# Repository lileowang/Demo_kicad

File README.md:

# Demo_kicad
Demo how to use Kicad for capturing circuit schematics and PCB layout

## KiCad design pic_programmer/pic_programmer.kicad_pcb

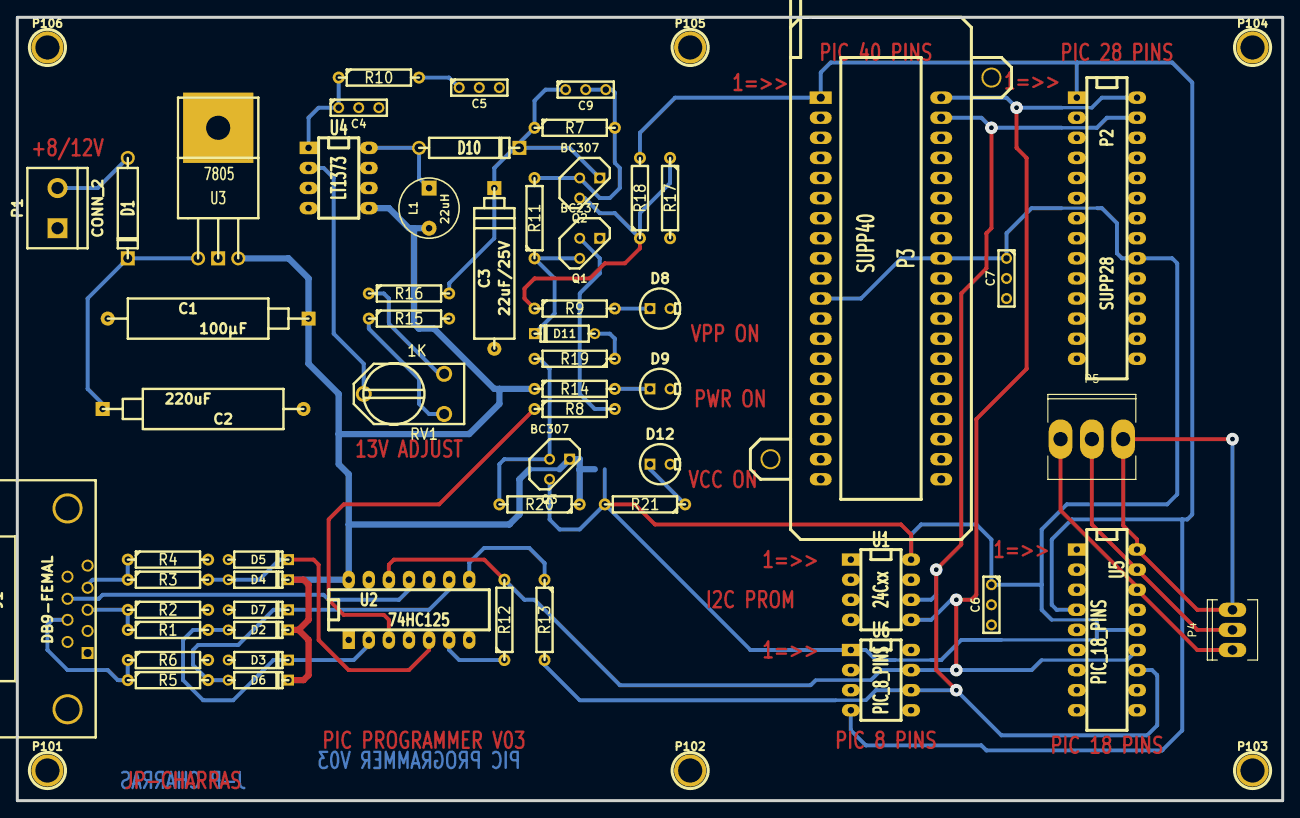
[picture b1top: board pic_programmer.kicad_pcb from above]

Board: 2 copper layers, 160.0 x 99.1 mm, 65 parts (1 on the bottom side), 37 nets.

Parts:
C1: 100µF; CP10
C2: 220uF; CP10
C3: 22uF/25V; CP8
C4: 0; C1-1
C5: 10nF; C1-1
C6, C7: 100nF; C1-1
C9: 220nF; C1-1
D1: 1N4004; D5
D2, D3, D4, D5, D6, D7, D11: BAT43; D3
D8: RED-LED; LEDV
D9: GREEN-LED; LEDV
D10: SCHOTTKY; D5
D12: YELLOW-LED; LEDV
J1: DB9-FEMAL; DB9FC
JP1: JUMPER; GS2
L1: 22uH; INDUCTOR_V
P1: CONN_2; bornier2
P2: SUPP28; DIP-28__300_ELL
P3: SUPP40; 40tex-Ell600
P4: CONN_01X03; Socket_MOLEX-KK-RM2-54mm_Lock_3pin_straight
P5: CONN_01X03; Socket_MOLEX-KK-RM3-96mm_Lock_3pin_straight
P101, P102, P103, P104, P105, P106: CONN_1; 1pin-4
Q1: BC237; TO92
Q2, Q3: BC307; TO92
R1, R2, R3, R4, R5, R6, R7: 10K; R4
R8: 1K; R4
R9, R19, R20: 2.2K; R4
R10: 5,1K; R4
R11, R17: 22K; R4
R12, R13, R14, R21: 470; R4
R15: 6.2K; R4
R16: 62K; R4
R18: 220; R4
RV1: 1K; RV2X4
U1: 24Cxx; DIP-8__300_ELL
U2: 74HC125; DIP-14__300_ELL
U3: 7805; LM78XX
U4: LT1373; DIP-8__300_ELL
U5: PIC_18_PINS; DIP-18__300_ELL
U6: PIC_8_PINS; DIP-8__300_ELL

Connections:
/CTS: J1.8, U2.11
/DTR: J1.4, R3.1, R4.1
/PC-CLOCK-OUT: J1.7, R5.1, R6.1
/TXD: J1.3, R1.1, R2.1
/pic_sockets/CLOCK-RB6: P2.27, P3.39, R13.2, U1.6, U5.12, U6.6
/pic_sockets/DATA-RB7: P2.28, P3.40, R12.2, U1.5, U2.12, U5.13, U6.7
/pic_sockets/VCC_PIC: C6.1, C7.1, JP1.2, P2.20, P3.11, P3.32, Q3.3, R21.2, U1.8, U5.14, U6.1
/pic_sockets/VPP-MCLR: P2.1, P3.1, R18.2, U5.4, U6.4
/pic_sockets/a1: P4.3, P5.3, U5.18
/pic_sockets/a2: P4.2, P5.2, U5.17
/pic_sockets/a3: P4.1, P5.1, U5.16
GND: C1.2, C2.2, C3.2, C4.2, C5.2, C6.2, C7.2, D3.1, D5.1, D7.1, D8.2, D9.2, D12.2, J1.5, P1.1, P2.8, P2.19, P3.8, P3.12, P3.31, Q1.1, R2.2, R4.2, R6.2, R15.2, R17.2, U1.1, U1.2, U1.3, U1.4, U2.1, U2.4, U2.7, U2.10, U2.13, U3.GND, U4.6, U4.7, U5.5, U6.8
unnamed: C2.1, D1.2, U3.VI
unnamed: C4.1, R10.1, U4.1
unnamed: C5.1, R10.2
unnamed: C9.2, Q2.2, R7.2, R11.2
unnamed: D1.1, P1.2
unnamed: D2.1, D3.2, R1.2, U2.2
unnamed: D4.1, D5.2, R3.2, U2.5
unnamed: D6.1, D7.2, R5.2, U2.9
unnamed: D8.1, R9.2
unnamed: D9.1, R14.2
unnamed: D10.1, L1.1, U4.8
unnamed: D11.1, R19.1
unnamed: D11.2, Q1.3, R11.1
unnamed: D12.1, R21.1
unnamed: Q1.2, R8.2
unnamed: Q2.3, R9.1, R17.1, R18.1
unnamed: Q3.2, R19.2, R20.2
unnamed: R8.1, U2.3
unnamed: R12.1, U2.6
unnamed: R13.1, U2.8
unnamed: R15.1, RV1.1
unnamed: R16.1, RV1.3
unnamed: RV1.2, U4.2
VCC: C1.1, D2.2, D4.2, D6.2, JP1.1, L1.2, Q3.1, R14.1, R20.1, U2.14, U3.VO, U4.5
VPP: C3.1, C9.1, D10.2, Q2.1, R7.1, R16.2

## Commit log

2019-05-31 Added PIC programmer project from Kicad installation folder as starting poing: C:\Program Files (x86)\KiCad\share\kicad\demos\pic_programmer
2019-05-31 added 2 1x3 connectors.
2019-05-31 added bus lines
2019-05-31 associated netlist with footprint in cvpcb for 2 sockets.
2019-05-31 generated netlist for pcb.
2019-05-31 imported the netlist into pcb.
2019-05-31 performanced pcb layout with free-router, added one extra track to practice key shortcuts: x, v
